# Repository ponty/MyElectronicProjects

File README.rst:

Hobby electronic projects built by me.

Most of them are built on stripboard.

Links:
 * home: https://github.com/ponty/MyElectronicProjects
 * documentation: http://ponty.github.com/MyElectronicProjects

Design tool: `EAGLE Light Edition`_

.. _`EAGLE Light Edition`: http://www.cadsoftusa.com/freeware.htm

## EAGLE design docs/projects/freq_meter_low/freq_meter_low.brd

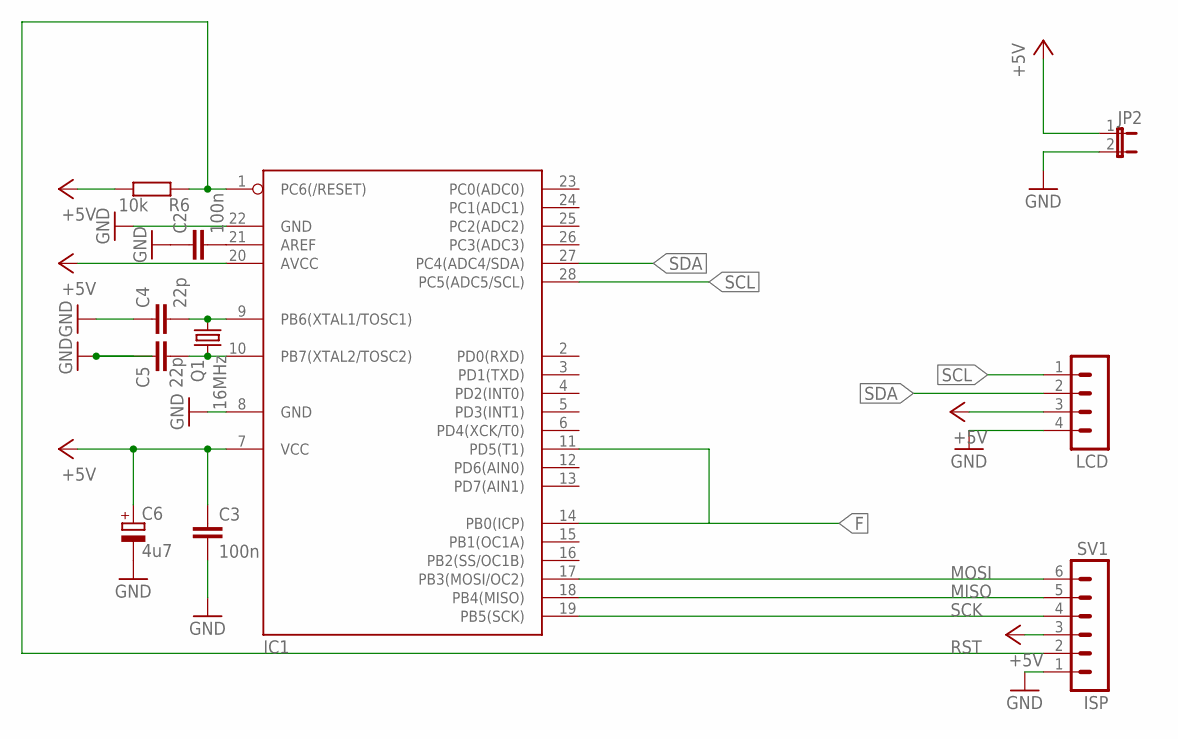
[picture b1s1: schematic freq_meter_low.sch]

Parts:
C2, C3: 100n; C025-024X044
C4: 22p; C025-024X044
C5: 22p; C050-025X075
C6: 4u7; TT2D5
IC1: MEGA8-P; DIL28-3
JP2: JP1E; JP1
LCD: MA04-1
Q1: 16MHz; TC26V
R6: 10k; 0204/5
SV1: ISP; MA06-1

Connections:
+5V: C3.1, C6.+, IC1.7 (VCC), IC1.20 (AVCC), JP2.1, LCD.3, R6.1, SV1.3
F: IC1.11 (PD5(T1)), IC1.14 (PB0(ICP))
GND: C2.1, C3.2, C4.1, C5.1, C6.-, IC1.8 (GND), IC1.22 (GND), JP2.2, LCD.4, SV1.1
MISO: IC1.18 (PB4(MISO)), SV1.5
MOSI: IC1.17 (PB3(MOSI/OC2)), SV1.6
unnamed: C2.2, IC1.21 (AREF)
unnamed: C4.2, IC1.9 (PB6(XTAL1/TOSC1)), Q1.2
unnamed: C5.2, IC1.10 (PB7(XTAL2/TOSC2)), Q1.1
RST: IC1.1 (PC6(/RESET)), R6.2, SV1.2
SCK: IC1.19 (PB5(SCK)), SV1.4
SCL: IC1.28 (PC5(ADC5/SCL)), LCD.1
SDA: IC1.27 (PC4(ADC4/SDA)), LCD.2

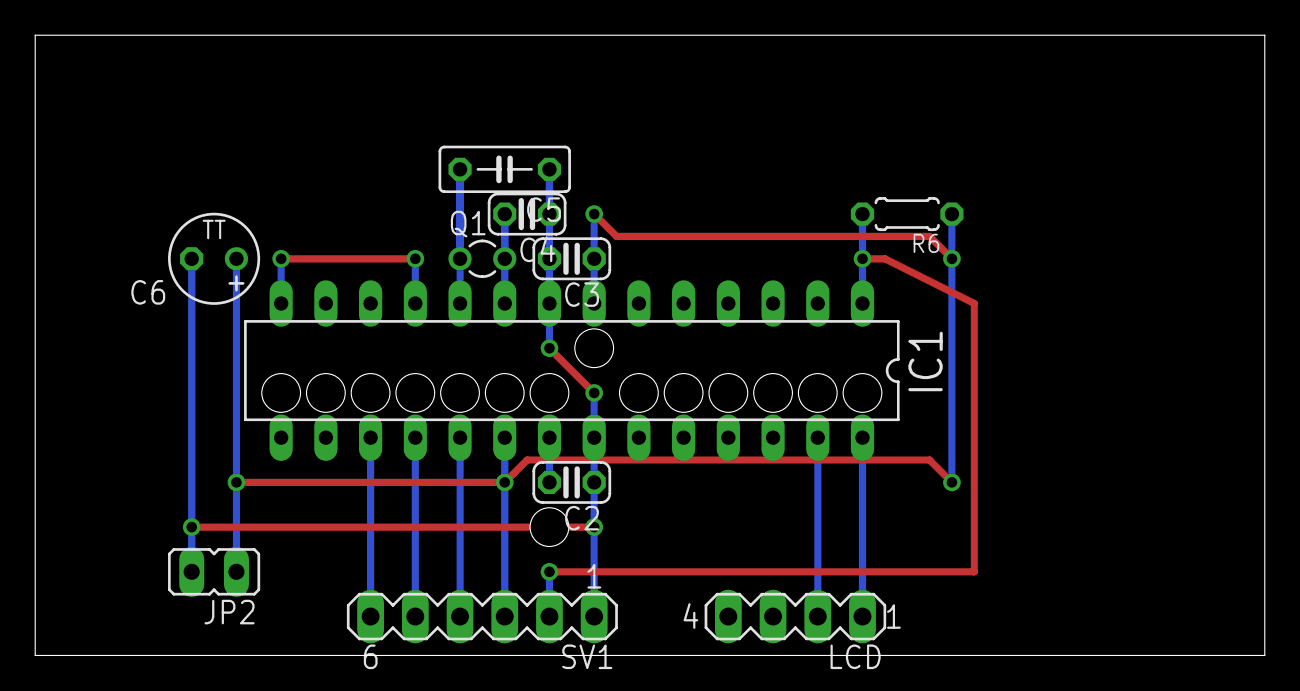
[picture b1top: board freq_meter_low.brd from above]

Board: 2 copper layers, 69.8 x 35.2 mm, 11 parts (0 on the bottom side), 12 nets.

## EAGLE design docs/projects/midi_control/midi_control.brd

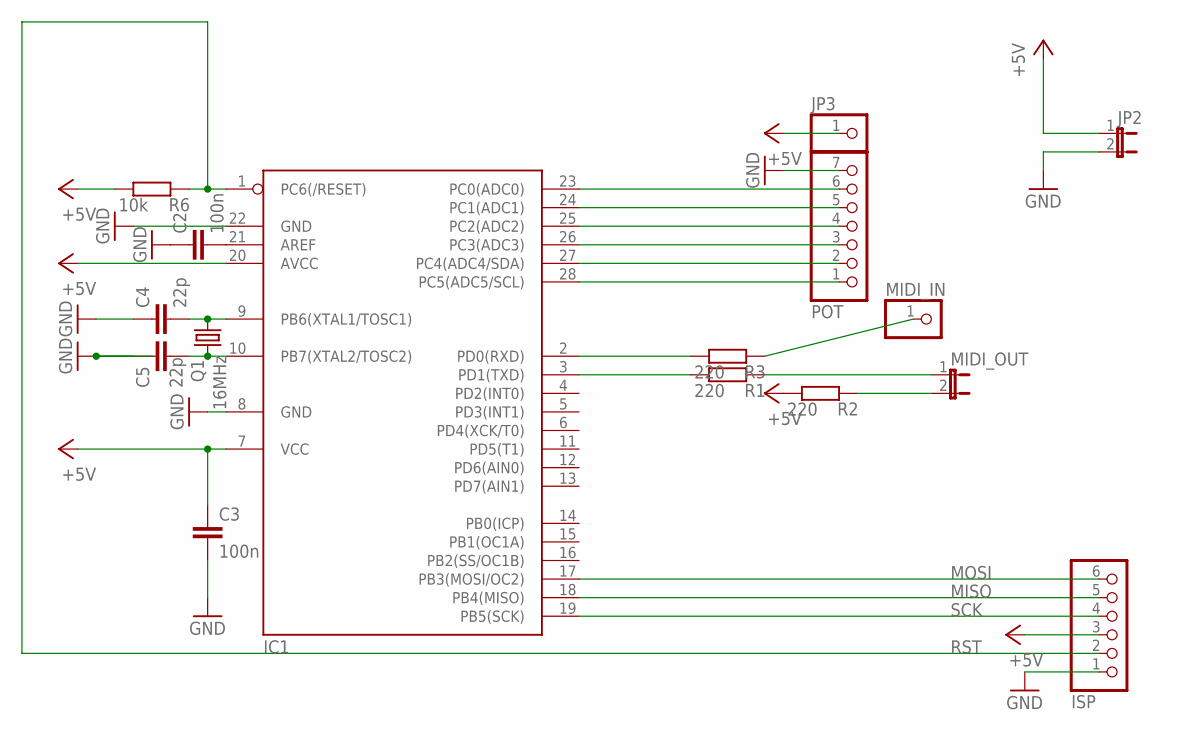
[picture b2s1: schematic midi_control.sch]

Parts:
C2, C3: 100n; C025-024X044
C4: 22p; C025-024X044
C5: 22p; C050-025X075
IC1: MEGA8-P; DIL28-3
ISP: PINHD-1X6/90; 1X06/90
JP2: JP1E; JP1
JP3: PINHD-1X1; 1X01
MIDI_IN: PINHD-1X1; 1X01
MIDI_OUT: JP1E; JP1
POT: PINHD-1X7; 1X07
Q1: 16MHz; TC26V
R1, R3: 220; 0207/10
R2: 220; R0805
R6: 10k; 0207/15

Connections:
+5V: C3.1, IC1.7 (VCC), IC1.20 (AVCC), ISP.3, JP2.1, JP3.1, R2.1, R6.1
GND: C2.1, C3.2, C4.1, C5.1, IC1.8 (GND), IC1.22 (GND), ISP.1, JP2.2, POT.7
MISO: IC1.18 (PB4(MISO)), ISP.5
MOSI: IC1.17 (PB3(MOSI/OC2)), ISP.6
unnamed: C2.2, IC1.21 (AREF)
unnamed: IC1.2 (PD0(RXD)), R3.1
unnamed: IC1.3 (PD1(TXD)), R1.1
unnamed: MIDI_OUT.1, R1.2
unnamed: MIDI_OUT.2, R2.2
unnamed: IC1.23 (PC0(ADC0)), POT.6
unnamed: IC1.24 (PC1(ADC1)), POT.5
unnamed: IC1.25 (PC2(ADC2)), POT.4
unnamed: IC1.26 (PC3(ADC3)), POT.3
unnamed: IC1.27 (PC4(ADC4/SDA)), POT.2
unnamed: IC1.28 (PC5(ADC5/SCL)), POT.1
unnamed: MIDI_IN.1, R3.2
unnamed: C4.2, IC1.9 (PB6(XTAL1/TOSC1)), Q1.2
unnamed: C5.2, IC1.10 (PB7(XTAL2/TOSC2)), Q1.1
RST: IC1.1 (PC6(/RESET)), ISP.2, R6.2
SCK: IC1.19 (PB5(SCK)), ISP.4

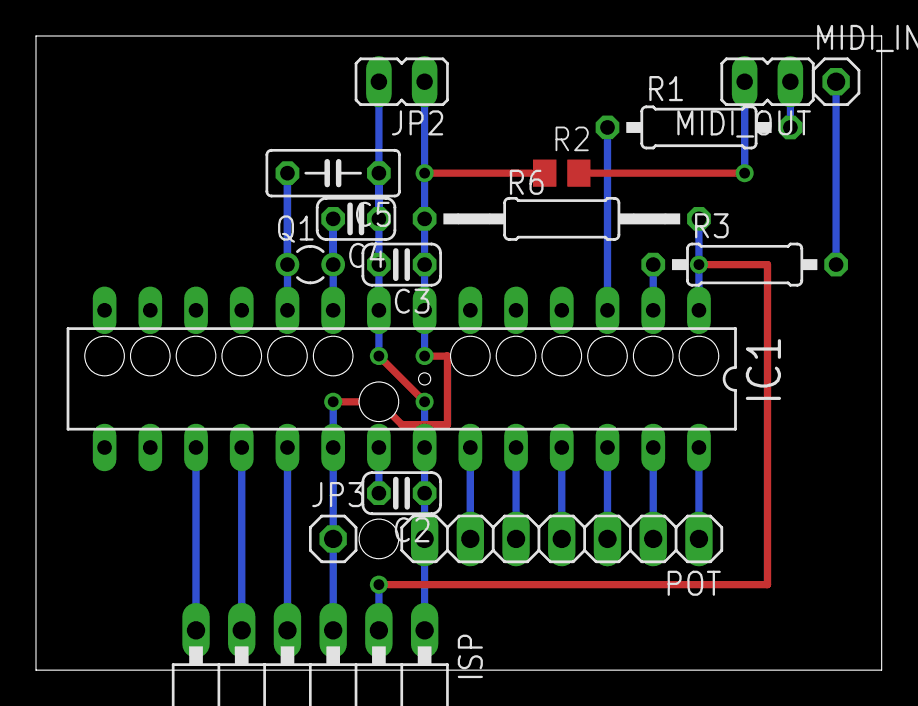
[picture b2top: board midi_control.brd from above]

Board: 2 copper layers, 47.0 x 35.2 mm, 16 parts (0 on the bottom side), 20 nets.

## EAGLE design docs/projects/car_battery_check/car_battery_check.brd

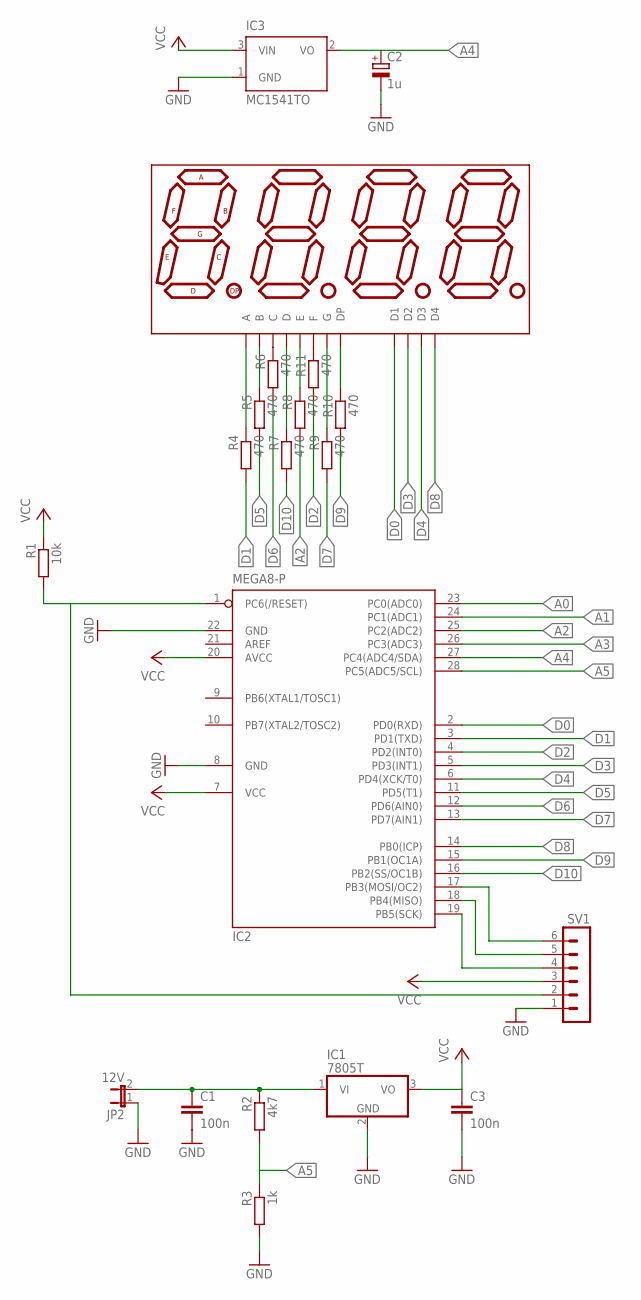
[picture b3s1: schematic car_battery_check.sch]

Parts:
C1, C3: 100n; C025-024X044
C2: 1u; E2,5-6E
IC1: 7805T; TO220H
IC2: MEGA8-P; DIL28-3
IC3: MC1541TO; TO92
JP2: 12V; JP1
R1: 10k; 0617/17
R2: 4k7; R2512
R3: 1k; 0207/15
R4, R6, R9, R10, R11: 470; 0204/7
R5: 470; 0207/10
R7: 470; 0207/12
R8: 470; 0207/15
SV1: MA06-1
U$1: 7-SEGMENT-4DIGIT-COUNTERPTH; 7-SEGMENT-4DIGIT-COUNTER

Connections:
A0: IC2.23 (PC0(ADC0))
A1: IC2.24 (PC1(ADC1))
A2: IC2.25 (PC2(ADC2)), R8.2
A3: IC2.26 (PC3(ADC3))
A4: C2.+, IC2.27 (PC4(ADC4/SDA)), IC3.2 (VO)
A5: IC2.28 (PC5(ADC5/SCL)), R2.2, R3.1
D0: IC2.2 (PD0(RXD)), U$1.12 (D1)
D1: IC2.3 (PD1(TXD)), R4.2
D2: IC2.4 (PD2(INT0)), R11.2
D3: IC2.5 (PD3(INT1)), U$1.9 (D2)
D4: IC2.6 (PD4(XCK/T0)), U$1.8 (D3)
D5: IC2.11 (PD5(T1)), R5.2
D6: IC2.12 (PD6(AIN0)), R6.2
D7: IC2.13 (PD7(AIN1)), R9.2
D8: IC2.14 (PB0(ICP)), U$1.6 (D4)
D9: IC2.15 (PB1(OC1A)), R10.2
D10: IC2.16 (PB2(SS/OC1B)), R7.2
GND: C1.2, C2.-, C3.2, IC1.2 (GND), IC2.8 (GND), IC2.22 (GND), IC3.1 (GND), JP2.1, R3.2, SV1.1
unnamed: C1.1, IC1.1 (VI), JP2.2, R2.1
unnamed: R4.1, U$1.11 (A)
unnamed: R5.1, U$1.7 (B)
unnamed: R6.1, U$1.4 (C)
unnamed: IC2.19 (PB5(SCK)), SV1.4
unnamed: IC2.18 (PB4(MISO)), SV1.5
unnamed: IC2.17 (PB3(MOSI/OC2)), SV1.6
unnamed: R7.1, U$1.2 (D)
unnamed: R8.1, U$1.1 (E)
unnamed: R9.1, U$1.5 (G)
unnamed: R10.1, U$1.3 (DP)
unnamed: R11.1, U$1.10 (F)
unnamed: IC2.1 (PC6(/RESET)), R1.2, SV1.2
VCC: C3.1, IC1.3 (VO), IC2.7 (VCC), IC2.20 (AVCC), IC3.3 (VIN), R1.1, SV1.3

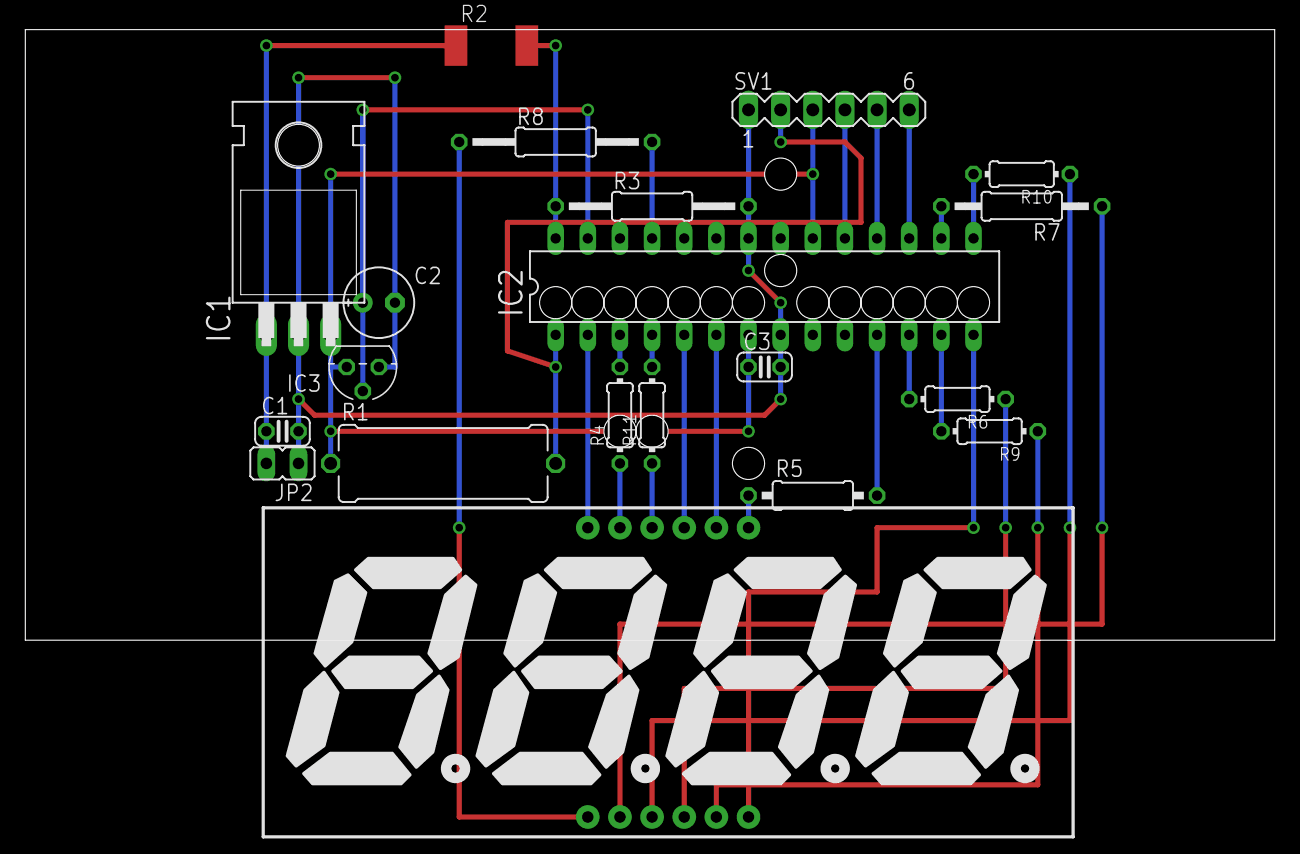
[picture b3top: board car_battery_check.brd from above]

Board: 2 copper layers, 98.7 x 48.2 mm, 20 parts (0 on the bottom side), 29 nets.

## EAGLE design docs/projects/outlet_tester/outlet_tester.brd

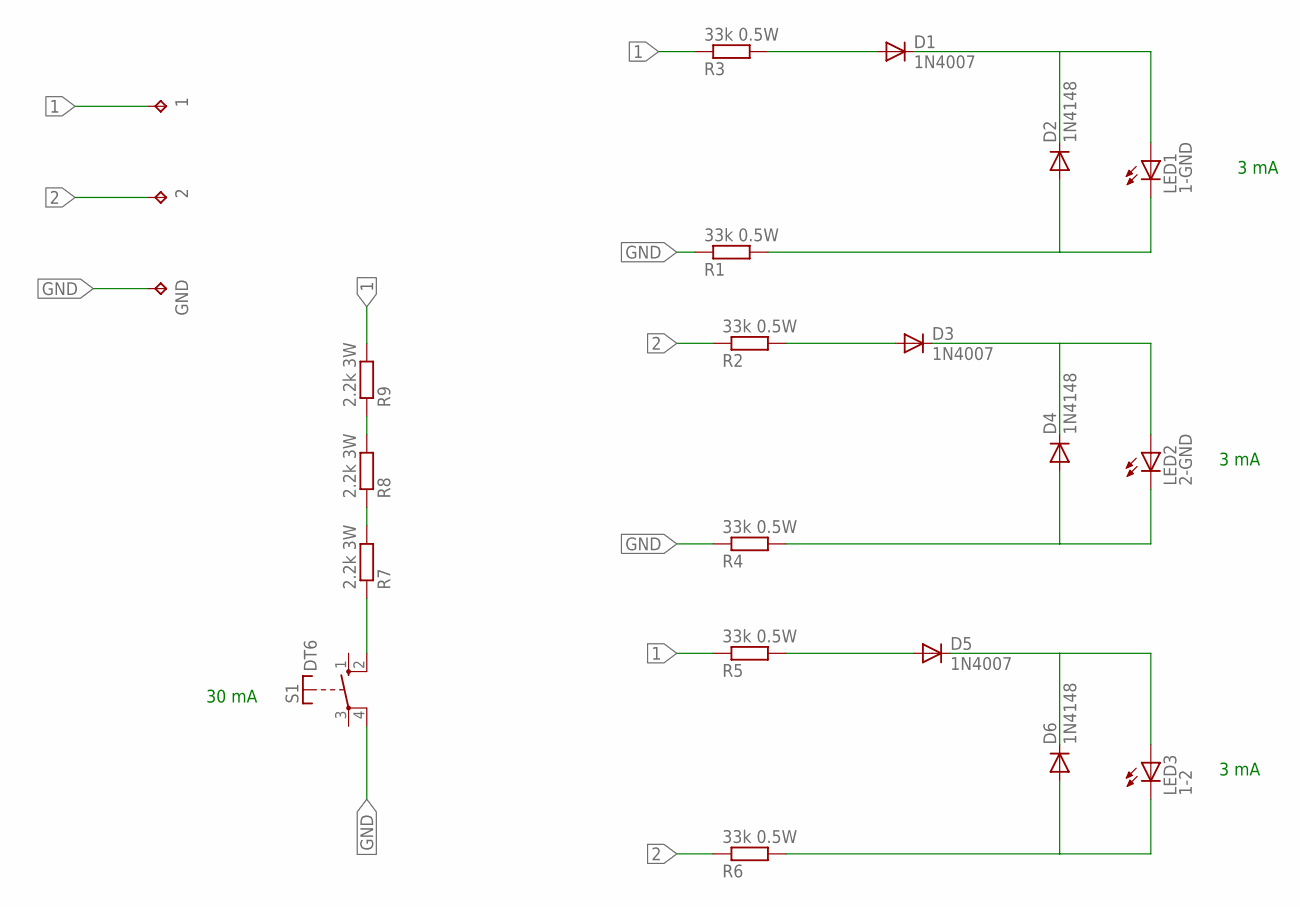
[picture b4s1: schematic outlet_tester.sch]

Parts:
1, 2: TPPAD1-20; P1-20
D1, D3, D5: 1N4007; D-10
D2, D4, D6: 1N4148; D-10
GND: TPPAD1-20; P1-20
LED1: 1-GND; LED5MM
LED2: 2-GND; LED5MM
LED3: 1-2; LED5MM
R1, R2, R3, R4, R5, R6: 33k 0.5W; 0207/10
R7, R8, R9: 2.2k 3W; 0207/10
S1: DT6

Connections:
1: 1.TP, R3.1, R5.1, R9.2
2: 2.TP, R2.1, R6.1
GND: GND.TP, R1.1, R4.1, S1.4
unnamed: R7.1, S1.2 (S)
unnamed: D1.C, D2.C, LED1.A
unnamed: D2.A, LED1.K (C), R1.2
unnamed: D1.A, R3.2
unnamed: D3.A, R2.2
unnamed: D5.A, R5.2
unnamed: D3.C, D4.C, LED2.A
unnamed: D4.A, LED2.K (C), R4.2
unnamed: R7.2, R8.1
unnamed: R8.2, R9.1
unnamed: D5.C, D6.C, LED3.A
unnamed: D6.A, LED3.K (C), R6.2

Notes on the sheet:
30 mA
3 mA

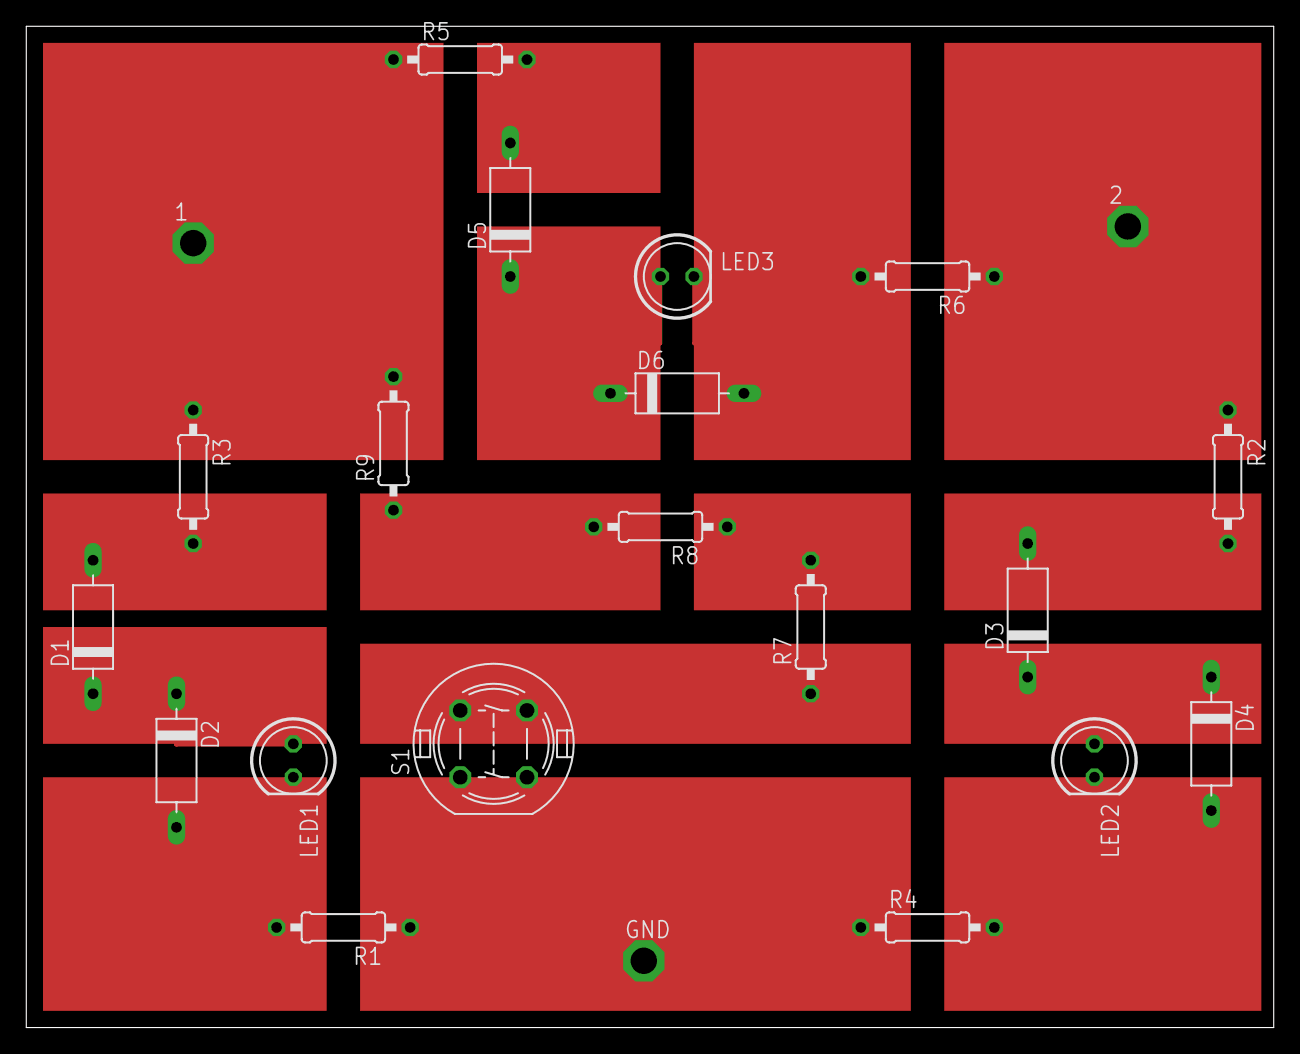
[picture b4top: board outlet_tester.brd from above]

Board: 2 copper layers, 94.9 x 76.2 mm, 22 parts (0 on the bottom side), 15 nets.

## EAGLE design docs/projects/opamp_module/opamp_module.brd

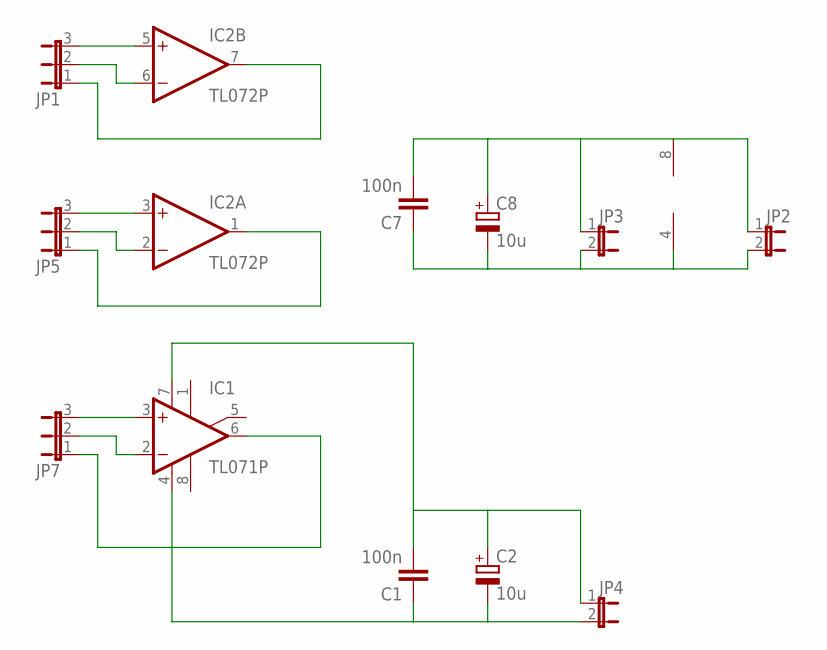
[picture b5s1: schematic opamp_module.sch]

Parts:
C1, C7: 100n; C025-024X044
C2, C8: 10u; E2,5-5
IC1: TL071P; DIL08
IC2: TL072P; DIL08
JP1, JP5, JP7: JP2E; JP2
JP2, JP3, JP4: JP1E; JP1

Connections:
unnamed: IC2.2 (-IN), JP5.2
unnamed: C7.1, C8.-, IC2.4 (V-), JP2.2, JP3.2
unnamed: IC2.3 (+IN), JP5.3
unnamed: IC2.1 (OUT), JP5.1
unnamed: IC2.5 (+IN), JP1.3
unnamed: IC2.6 (-IN), JP1.2
unnamed: IC2.7 (OUT), JP1.1
unnamed: C7.2, C8.+, IC2.8 (V+), JP2.1, JP3.1
unnamed: C1.1, C2.-, IC1.4 (V-), JP4.2
unnamed: IC1.3 (+IN), JP7.3
unnamed: IC1.2 (-IN), JP7.2
unnamed: IC1.6 (OUT), JP7.1
unnamed: C1.2, C2.+, IC1.7 (V+), JP4.1

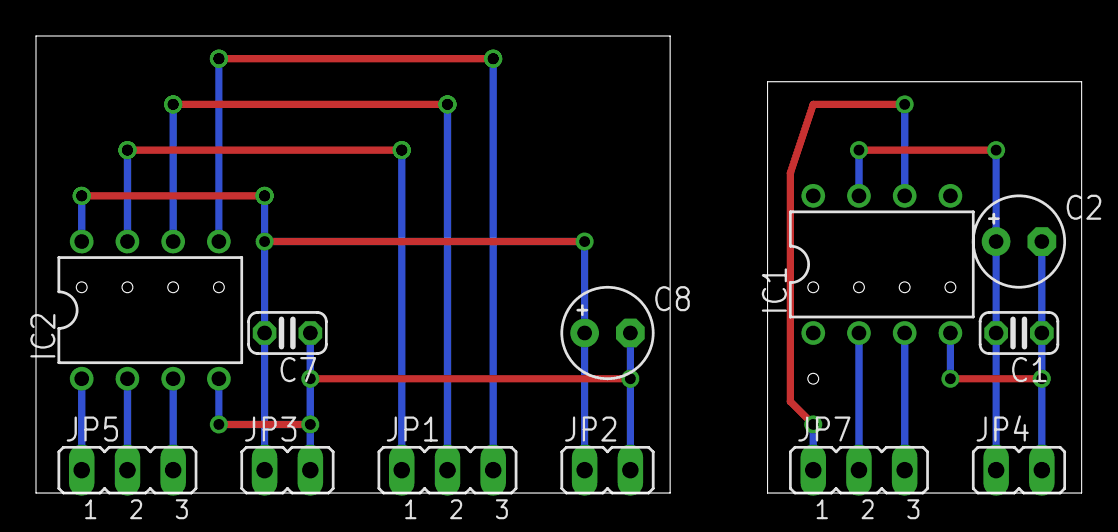
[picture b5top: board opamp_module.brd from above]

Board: 2 copper layers, 58.1 x 25.4 mm, 12 parts (0 on the bottom side), 13 nets.

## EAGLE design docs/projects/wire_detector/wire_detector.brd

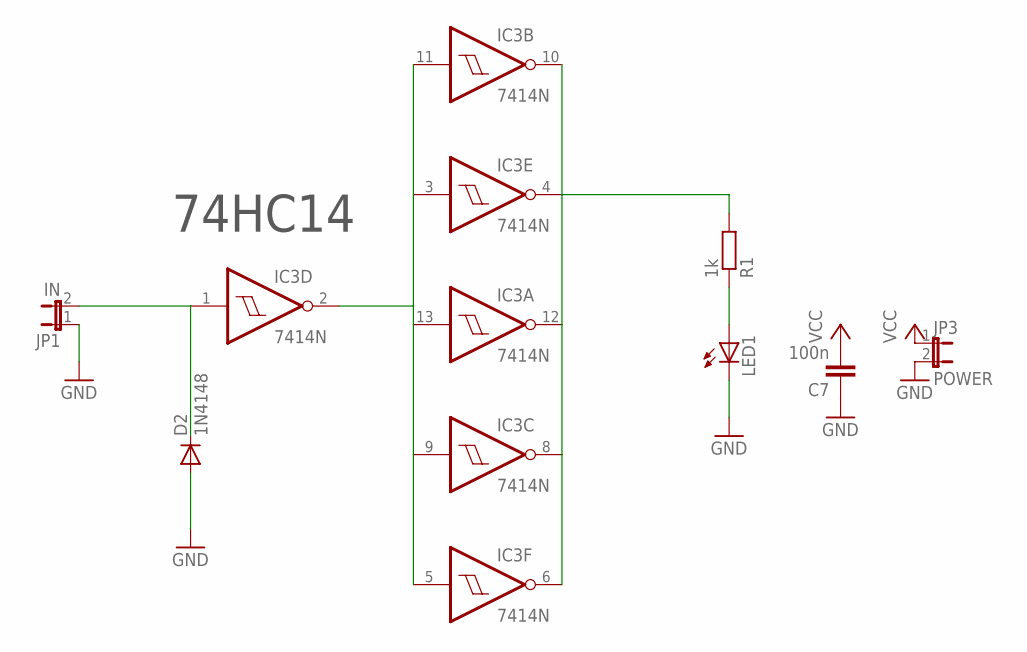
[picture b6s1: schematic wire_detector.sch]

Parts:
C7: 100n; C025-024X044
D2: 1N4148; D-2.5
IC3: 7414N; DIL14
JP1: IN; JP1
JP3: POWER; JP1
LED1: LED5MM
R1: 1k; 0204/5

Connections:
GND: C7.1, D2.A, IC3.7 (GND), JP1.1, JP3.2, LED1.K (C)
unnamed: IC3.4 (O), IC3.6 (O), IC3.8 (O), IC3.10 (O), IC3.12 (O), R1.2
unnamed: LED1.A, R1.1
unnamed: IC3.2 (O), IC3.3 (I), IC3.5 (I), IC3.9 (I), IC3.11 (I), IC3.13 (I)
unnamed: D2.C, IC3.1 (I), JP1.2
VCC: C7.2, IC3.14 (VCC), JP3.1

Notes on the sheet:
74HC14

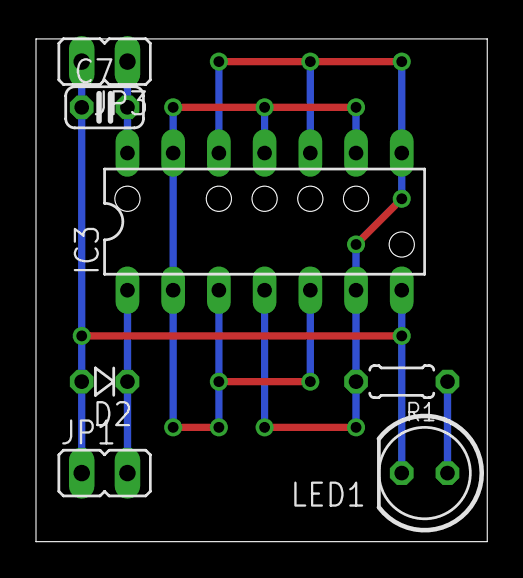
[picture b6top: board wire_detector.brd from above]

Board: 2 copper layers, 25.1 x 27.9 mm, 7 parts (0 on the bottom side), 6 nets.

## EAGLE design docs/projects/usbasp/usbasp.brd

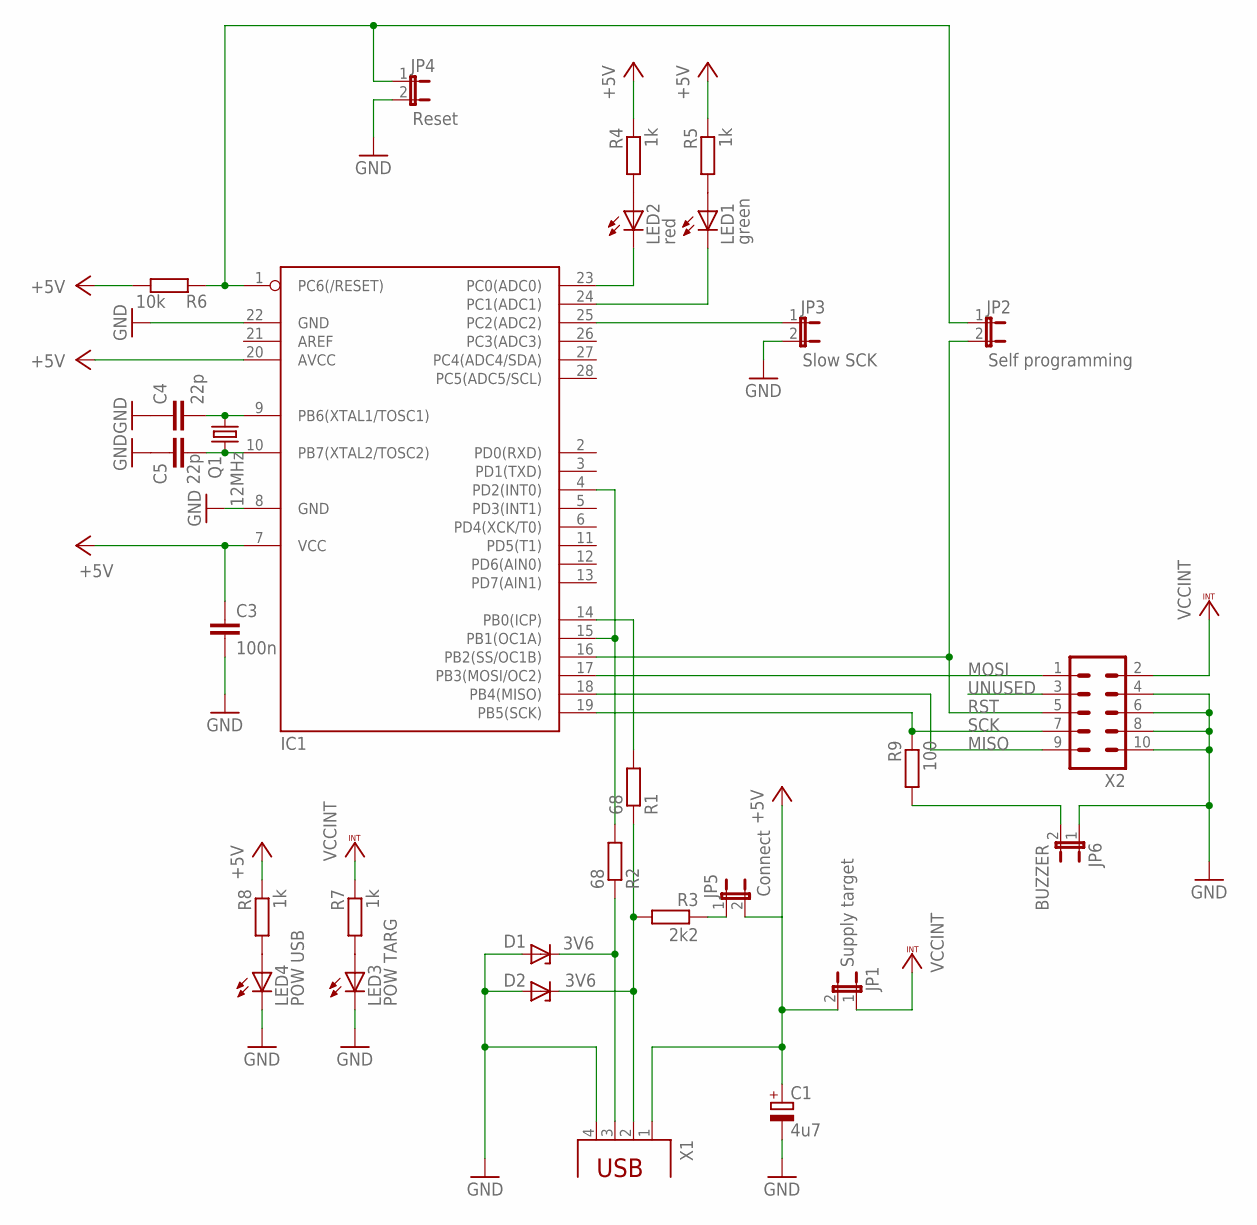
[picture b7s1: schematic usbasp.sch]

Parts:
C1: 4u7; TT5D6
C3: 100n; C025-024X044
C4: 22p; C025-024X044
C5: 22p; C050-025X075
D1: 3V6; DO34Z7
D2: 3V6; ZDIO-5
IC1: MEGA8-P; DIL28-3
JP1: Supply target; JP1
JP2: Self programming; JP1
JP3: Slow SCK; JP1
JP4: Reset; JP1
JP5: Connect; JP1
JP6: BUZZER; JP1
LED1: green; LED3MM
LED2: red; LED3MM
LED3: POW TARG; LED3MM
LED4: POW USB; LED3MM
Q1: 12MHz; TC26V
R1: 68; R1206
R2: 68; 0204V
R3: 2k2; 0617/17
R4, R8: 1k; 0204/5
R5: 1k; 0207/12
R6: 10k; 0207/15
R7: 1k; 0204V
R9: 100; 0207/15
X1: PN61729
X2: ML10L

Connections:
MISO: IC1.18 (PB4(MISO)), X2.9
MOSI: IC1.17 (PB3(MOSI/OC2)), X2.1
unnamed: LED3.A, R7.2
unnamed: D1.C, R2.1, X1.3
unnamed: C1.+, C3.1, IC1.7 (VCC), IC1.20 (AVCC), JP1.2, JP5.2, R4.1, R5.1, R6.1, R8.1, X1.1
unnamed: LED4.A, R8.2
unnamed: D2.C, R1.1, R3.2, X1.2
unnamed: JP5.1, R3.1
unnamed: IC1.4 (PD2(INT0)), IC1.15 (PB1(OC1A)), R2.2
unnamed: JP6.2, R9.2
unnamed: C1.-, C3.2, C4.1, C5.1, D1.A, D2.A, IC1.8 (GND), IC1.22 (GND), JP3.2, JP4.2, JP6.1, LED3.K (C), LED4.K (C), X1.4, X2.4, X2.6, X2.8, X2.10
unnamed: IC1.1 (PC6(/RESET)), JP2.1, JP4.1, R6.2
unnamed: IC1.25 (PC2(ADC2)), JP3.1
unnamed: LED2.A, R4.2
unnamed: IC1.23 (PC0(ADC0)), LED2.K (C)
unnamed: IC1.24 (PC1(ADC1)), LED1.K (C)
unnamed: IC1.14 (PB0(ICP)), R1.2
unnamed: C4.2, IC1.9 (PB6(XTAL1/TOSC1)), Q1.2
unnamed: C5.2, IC1.10 (PB7(XTAL2/TOSC2)), Q1.1
unnamed: LED1.A, R5.2
RST: IC1.16 (PB2(SS/OC1B)), JP2.2, X2.5
SCK: IC1.19 (PB5(SCK)), R9.1, X2.7
UNUSED: X2.3
VCCINT: JP1.1, R7.1, X2.2

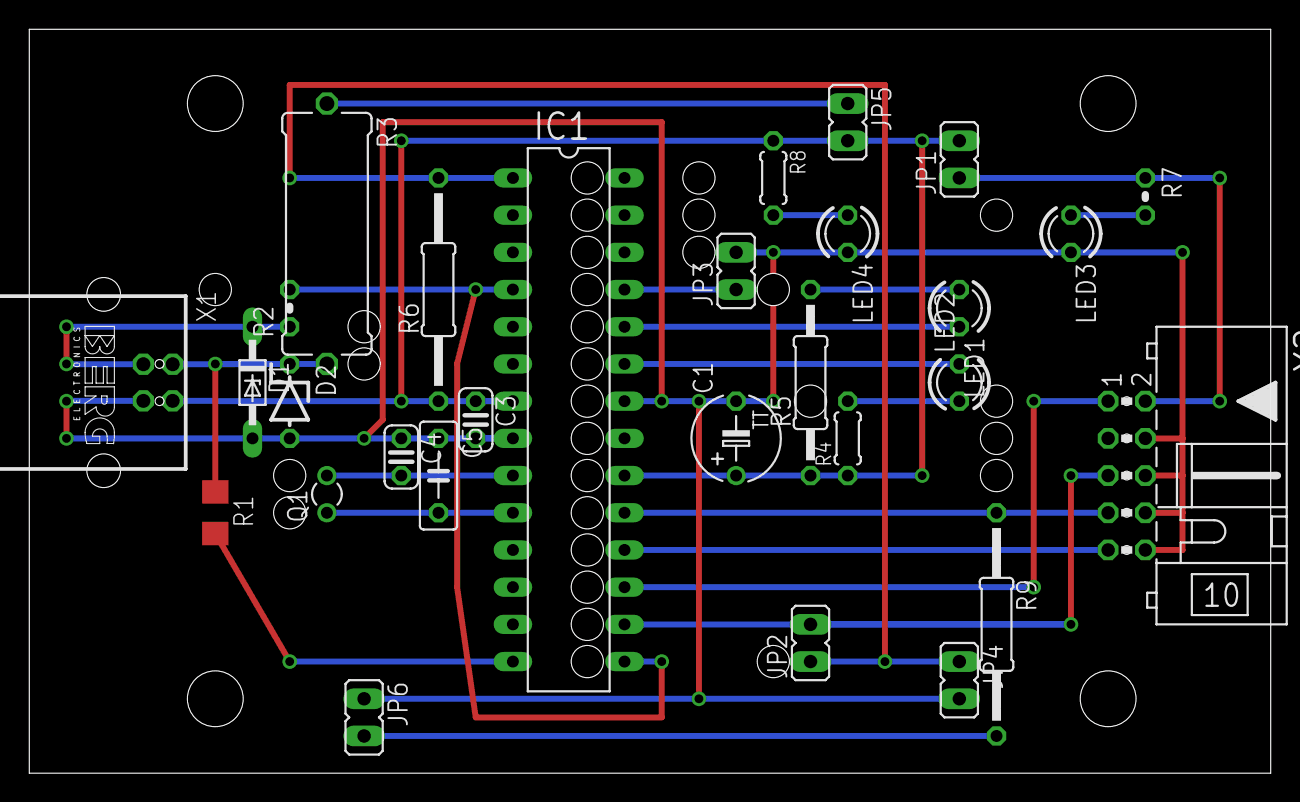
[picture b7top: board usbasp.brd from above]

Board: 2 copper layers, 84.8 x 50.8 mm, 29 parts (0 on the bottom side), 23 nets.

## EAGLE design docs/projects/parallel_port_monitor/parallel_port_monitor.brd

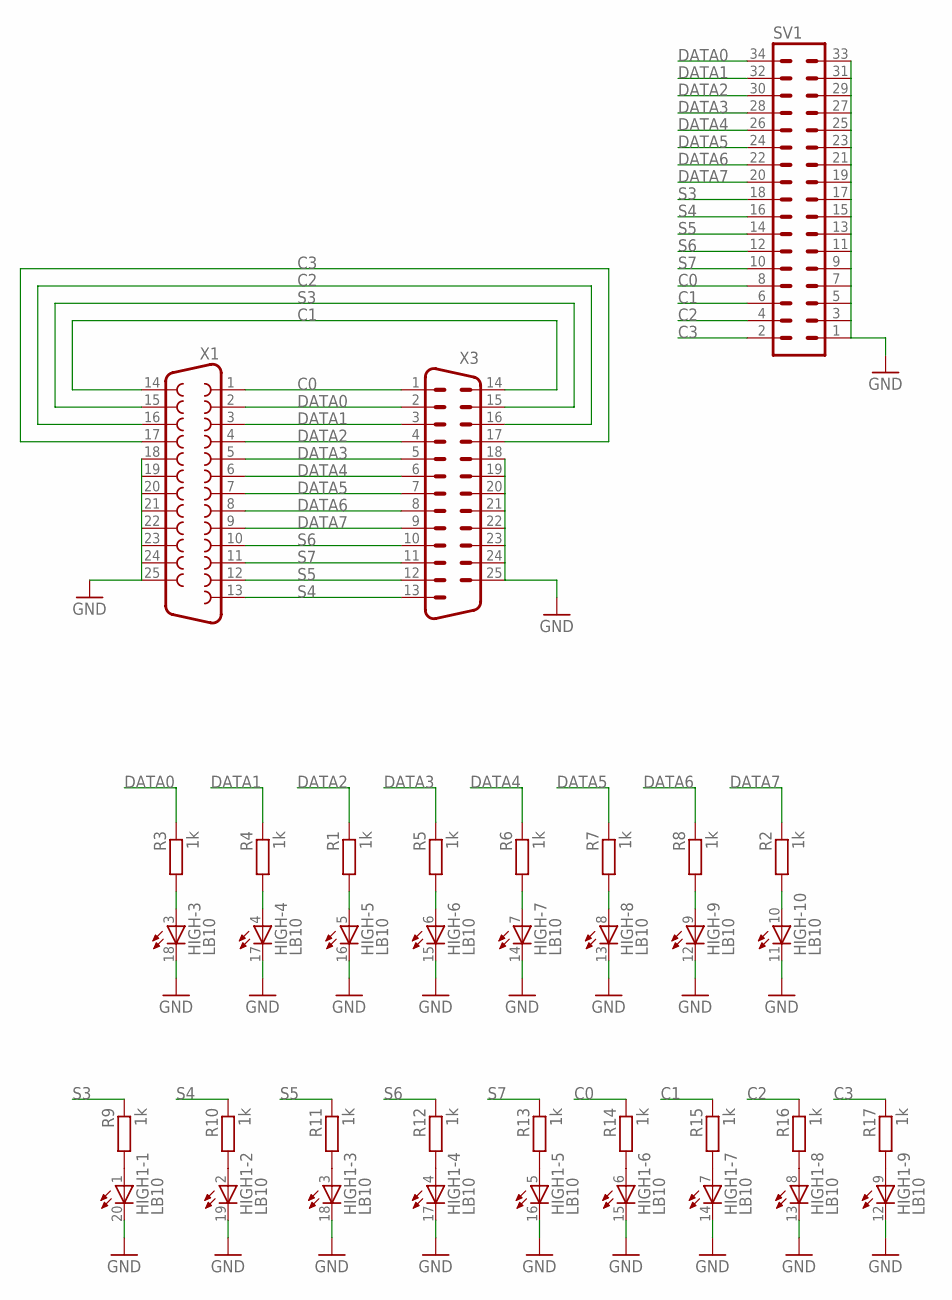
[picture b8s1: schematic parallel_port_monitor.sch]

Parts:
HIGH, HIGH1: LB10
R1, R2, R3, R4, R5, R6, R7, R8, R9, R10, R11, R12, R13, R14, R15, R16, R17: 1k; M0805
SV1: MA17-2W
X1: F25D
X3: M25D

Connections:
C0: R14.1, SV1.8, X1.1, X3.1
C1: R15.1, SV1.6, X1.14, X3.14
C2: R16.1, SV1.4, X1.16, X3.16
C3: R17.1, SV1.2, X1.17, X3.17
DATA0: R3.1, SV1.34, X1.2, X3.2
DATA1: R4.1, SV1.32, X1.3, X3.3
DATA2: R1.1, SV1.30, X1.4, X3.4
DATA3: R5.1, SV1.28, X1.5, X3.5
DATA4: R6.1, SV1.26, X1.6, X3.6
DATA5: R7.1, SV1.24, X1.7, X3.7
DATA6: R8.1, SV1.22, X1.8, X3.8
DATA7: R2.1, SV1.20, X1.9, X3.9
GND: HIGH.11 (C), HIGH.12 (C), HIGH.13 (C), HIGH.14 (C), HIGH.15 (C), HIGH.16 (C), HIGH.17 (C), HIGH.18 (C), HIGH1.12 (C), HIGH1.13 (C), HIGH1.14 (C), HIGH1.15 (C), HIGH1.16 (C), HIGH1.17 (C), HIGH1.18 (C), HIGH1.19 (C), HIGH1.20 (C), SV1.1, SV1.3, SV1.5, SV1.7, SV1.9, SV1.11, SV1.13, SV1.15, SV1.17, SV1.19, SV1.21, SV1.23, SV1.25, SV1.27, SV1.29, SV1.31, SV1.33, X1.18, X1.19, X1.20, X1.21, X1.22, X1.23, X1.24, X1.25, X3.18, X3.19, X3.20, X3.21, X3.22, X3.23, X3.24, X3.25
unnamed: HIGH.10 (A), R2.2
unnamed: HIGH1.1 (A), R9.2
unnamed: HIGH.3 (A), R3.2
unnamed: HIGH.4 (A), R4.2
unnamed: HIGH.6 (A), R5.2
unnamed: HIGH.5 (A), R1.2
unnamed: HIGH.7 (A), R6.2
unnamed: HIGH.8 (A), R7.2
unnamed: HIGH.9 (A), R8.2
unnamed: HIGH1.2 (A), R10.2
unnamed: HIGH1.3 (A), R11.2
unnamed: HIGH1.4 (A), R12.2
unnamed: HIGH1.5 (A), R13.2
unnamed: HIGH1.6 (A), R14.2
unnamed: HIGH1.7 (A), R15.2
unnamed: HIGH1.8 (A), R16.2
unnamed: HIGH1.9 (A), R17.2
S3: R9.1, SV1.18, X1.15, X3.15
S4: R10.1, SV1.16, X1.13, X3.13
S5: R11.1, SV1.14, X1.12, X3.12
S6: R12.1, SV1.12, X1.10, X3.10
S7: R13.1, SV1.10, X1.11, X3.11

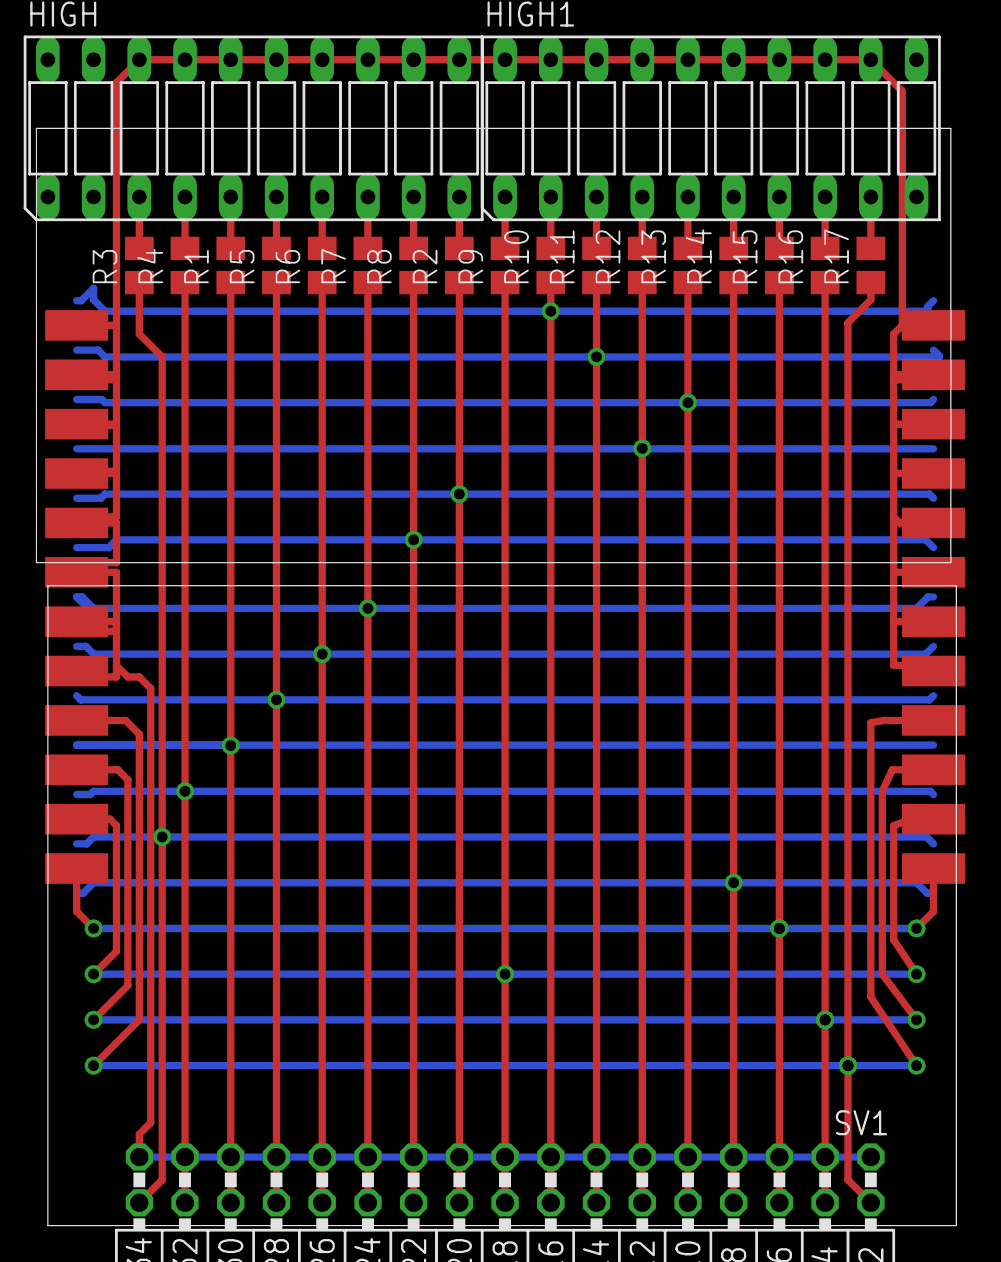
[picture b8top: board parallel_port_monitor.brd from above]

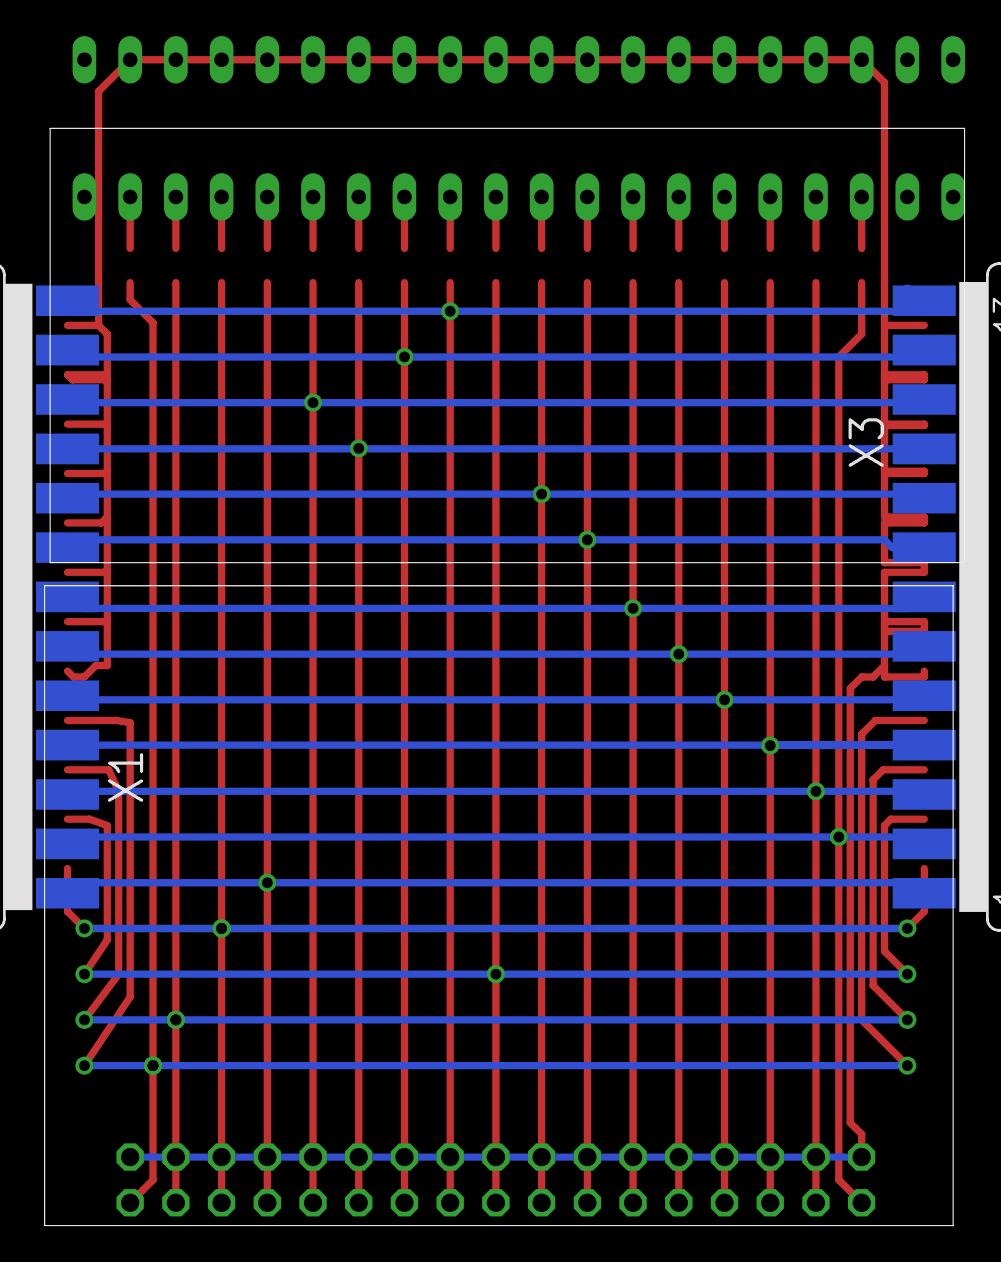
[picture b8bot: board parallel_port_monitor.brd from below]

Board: 2 copper layers, 51.1 x 61.0 mm, 22 parts (2 on the bottom side), 35 nets.

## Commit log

2011-12-28 start
2011-12-28 Update documentation
2012-03-12 config changed
2012-03-12 new: audio amp
2012-04-21 page break
2012-04-21 new: usb1wire
2012-04-21 new: opamp_module
2012-04-21 new: wire_detector
2012-04-21 new: alarm
2012-10-30 ignore *~
2012-10-30 new projects
2012-10-30 new 1wire ports
2012-10-30 usbasp
2012-10-30 remove unused files
2012-10-30 convert to eagle XML
2012-11-13 alarm: new debug
2012-11-13 ISP doc
2012-11-13 gif -> png (for pdf)
2012-11-13 use png
2012-11-13 pong
2012-11-13 gif -> png
2012-11-14 rename
2012-11-14 new proj
2012-12-02 more doc
2012-12-03 formatting by autopep8
2013-01-29 new: car battery check
2013-01-29 usbasp: labels
2013-01-29 usbasp: rotate labels
2013-02-13 fix airwires
2013-03-02 new: rs232 interface
2013-03-17 simplified pavement tasks
2013-03-17 local images
2013-03-17 outlet tester: adjust to available parts
2013-08-11 carbattery: adding voltage reference (MC1541)
2014-04-09 new midi controller
2014-04-09 fix link
2014-04-09 fix formatting
2014-04-09 lcd: document connections
2014-04-09 new freqmeter

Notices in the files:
parts and their libraries:
SparkFun-Displays: Licensing: CC v3.0 Share-Alike You are welcome to use this library for commercial purposes.
